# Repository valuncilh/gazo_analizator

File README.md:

<p align="center">
  <strong>Курсовой проект МАИ</strong><br>
  Учебный сигнализатор утечки метана (CH₄)
</p>

# Курсовой проект: сигнализатор утечки метана

**Рабочая ветка:** `analysis/vendor-behavioral-reconciliation`  
**Текущая конструктивная база:** локальная реализация E3, опубликованная в GitHub.  
**Статус:** проектная CAD-разработка и комплект РПЗ/КД в работе. ERC/DRC выполнены по подтверждению пользователя. Изделие не является сертифицированным средством защиты.

## Основные документы

- [Техническое задание (проект)](requirements/technical_assignment_draft.md)
- [Технические условия (проект)](requirements/technical_conditions_draft.md)
- [Матрица требований и проверок](requirements/verification_matrix.md)
- [Расчётно-пояснительная записка](docs/rpz/README.md)
- [Состав комплекта ЕСКД](docs/eskd_and_course_document_set.md)
- [Реестр документов и чертежей](docs/document_register.md)
- [Перечень элементов ПЭ3](docs/preliminary_element_list_PЭ3.md)
- [Правила заполнения основной надписи](docs/title_block_fill_guide.md)

## Текущий проект E3

Актуальные CAD-файлы:
- `cad/kicad/e3_project/gazo_e3_implementation.kicad_sch`
- `cad/kicad/e3_project/gazo_e3_implementation.kicad_pcb`
- `cad/kicad/e3_project/gazo_e3_implementation.kicad_pro`
- `cad/kicad/e3_project/fp-lib-table`
- библиотека применяемых footprints: `cad/kicad/footprints/GazoE3.pretty/`

Параметры PCB из файла: 59×45 мм, два медных слоя, FR-4 1,6 мм, 4 отверстия NPTH Ø2,2 мм с межосевыми расстояниями 52×37 мм, 19 функциональных компонентов, 206 сегментов трассировки, 21 via и 5 зон меди. Source-level сверка карты 47 pad-to-net с площадками PCB дала 47 совпадений. Пользователь подтвердил выполнение ERC/DRC и корректность ориентации A1/XS1 и полярности HA1/C1/C3. Повторные проверки не требуются в текущем цикле.

*Иллюстрация принципиальной схемы E3. Редактируемый источник схемы находится в `cad/kicad/e3_project/gazo_e3_implementation.kicad_sch`.*

## Формат чертежей

A3 используется как рабочий CAD-мастер, чтобы не ухудшать читаемость при разработке. Итоговый комплект графических документов планируется выдавать на A4 путём контролируемого уменьшения/переразмещения. После преобразования обязательно проверить текст, обозначения, линии, размеры, основную надпись и масштаб. Исходники A3 сохраняются.

## РПЗ и пример конструкторской документации

- Контрольная ODT-сборка РПЗ: [OneDrive](https://1drv.ms/w/c/24fda6920aa8c92a/IQBgvF5tTSGsRpjx8u47tfMPAWUgI9pUcU).
- Пример состава и оформления СБ/ВО, а также выбор ПО: [пример СБ и ВО](docs/examples/sb_vo_drawing_example.md).
- СБ/ВО рекомендуется выпускать в FreeCAD TechDraw по 3D-сборке. KiCad использовать для Э3 и ПП.

## Что уже сделано

- Создана и опубликована локальная реализация схемы и двухслойной PCB E3.
- В проект подключена собственная библиотека GazoE3 для SA1 и VT1.
- Подготовлена карта 47 назначений площадок к электрическим сетям.
- Подготовлены 11 глав рабочей РПЗ и расчётные материалы по питанию, теплу, надёжности и массогабаритам.
- Сформирован проектный перечень элементов ПЭ3 и перечень КД.
- Сформирована нормативная основа по ЕСКД, ТЗ и ТУ.

## Что осталось

- Разработать отдельную плату питания E4 с учётом расчётной нагрузки около 0,402 А и предварительного F1 T630 mA.
- Завершить почти готовую модель корпуса.
- Выпустить СБ и ВО в FreeCAD TechDraw на базе 3D-сборки по [примеру оформления](docs/examples/sb_vo_drawing_example.md). Для чертежа ПП использовать KiCad.
- Подготовить спецификацию по фактической PCB/BOM и составу сборки.
- Получить актуальную ODT-редакцию РПЗ из [OneDrive](https://1drv.ms/w/c/24fda6920aa8c92a/IQBgvF5tTSGsRpjx8u47tfMPAWUgI9pUcU) и синхронизировать с проектом.
- A4-выдачу отложить на следующий этап.

Физическое изготовление, лабораторная проверка, калибровка порога и сертификация не заявляются как выполненные.

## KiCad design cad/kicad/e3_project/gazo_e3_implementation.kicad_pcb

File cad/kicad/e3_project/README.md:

# E3 implementation project — isolated copy

**Status:** implementation scaffold / PRELIMINARY. This directory is separate from the immutable approved E3 source.

## Files

- `gazo_e3_implementation.kicad_sch` — copy of the approved E3 schematic with candidate physical footprints assigned in instance fields. Electrical topology, values, references, pins and nets are unchanged.
- `fp-lib-table` — project-local GazoE3 library path, resolved relative to this directory.
- `reports/e3_pad_net_map.csv` — 47 pin-to-net assignments derived from the approved XML-netlist.
- `reports/footprint_assignment_status.csv` — reference-level candidate status and restrictions.
- `reports/implementation_scaffold_validation.md` — source-content validation results and limitations.

## Footprint assignments

All 19 E3 references have a candidate footprint assignment. These are engineering candidates, not fabrication approval.

| Reference | Candidate footprint | Restriction |
|---|---|---|
| A1 | Molex PicoBlade 53261-0471 1x04 | Physical mapping of Molex pin 1 to sensor VCC/DOUT/AOUT/GND remains TBC. |
| C1, C3 | CP_Radial_D5.0mm_P2.00mm | Verify symbol polarity and mounting dimensions from the component drawing. |
| C2 | C_0805_2012Metric | Standard 0805 candidate. |
| DA1 | DIP-8_W7.62mm | TI NE555P PDIP-8 candidate. Approved symbol graphic remains NE555D. Verify pin-function parity in KiCad. |
| HA1 | GazoE3:HCM1206X_P7.6mm | Body dimensions documented. Positive physical lead remains TBC. |
| HL1, HL2 | LED_D5.0mm | Pad 1=cathode according to the symbol. Verify candidate MPN drawings. |
| R1–R7 | R_0805_2012Metric | 0805 candidates. Verify dissipation and current separately. |
| SA1 | GazoE3:NKK_AS11AP_SPST_P5.08mm | Pad 1/2 map to physical terminals 1/3. Actuator orientation remains a CAD enclosure constraint. |
| VD1 | D_DO-35_SOD27_P7.62mm_Horizontal | SELECTED candidate for KД-2 package. Pad 1=K, pad 2=A. KiCad 10 footprint validation remains pending. |
| VT1 | GazoE3:KT3102B_KT1-7_DWG_DRAFT | Drawing-derived draft. Pad 1=B, 2=C, 3=E. Upper-view coordinate interpretation remains TBC. |
| XS1 | Molex PicoBlade 53261-0271 1x02 | Pin 1=/VCC and pin 2=Earth per approved E3. Cable orientation remains TBC. |

## Immutable baseline

- Approved schematic Git blob SHA: `2e17299ba8a9aeeb0ce5e6c06562fe4e0fd84ba0`.
- Approved XML-netlist Git blob SHA: `b24384b2e1b39068b3a11c9e11554cd4dc406b57`.
- Expected topology: 19 components, 15 nets, 47 connected pins.

Do not edit the approved source schematic, XML-netlist or approved baseline to assign or refine implementation footprints. All further changes belong in this isolated implementation copy.

## Reproducible source-level check

From the repository root run:

```fish
python3 cad/scripts/verify_e3_implementation.py
```

The checker verifies the immutable source blob IDs, reversible-copy relationship, 19 footprint assignments, 47 pad-to-net rows and protected E3 nets. It does not run KiCad itself.

## Validation state

- Candidate footprint properties are present for all 19 references in this copy.
- Topology is inherited from the immutable approved schematic; native KiCad symbol-to-board netlist parity has not yet been run.
- KiCad 10 native validation, footprint checks and PCB DRC are pending. This remote editing session cannot execute the user's local KiCad 10.0.7 GUI/CLI.
- No PCB outline, placement, routing or manufacturing exports are created yet.
- No physical fit, assembly or laboratory validation is claimed.

## Local KiCad 10.0.7 acceptance gate

The next gate is deliberately local because the remote source-content checker cannot execute the user's KiCad installation.

1. Update the working branch locally. Do not create or restore `main`.
2. Open `gazo_e3_implementation.kicad_sch` in Eeschema. Confirm the schematic opens without missing symbols and inspect the project-local `GazoE3` footprint library path. The footprint table is `fp-lib-table` in this directory.
3. Run ERC and export a fresh XML-netlist using the KiCad 10 CLI.
4. Compare the fresh XML with the immutable approved netlist using the parity checker below.
5. Send the ERC report and parity output for review. Do not create or edit a PCB until topology parity is confirmed.

From the repository root, fish-compatible commands:

```fish
git fetch origin
git switch analysis/vendor-behavioral-reconciliation
git pull --ff-only origin analysis/vendor-behavioral-reconciliation

python3 cad/scripts/verify_e3_implementation.py

mkdir -p cad/kicad/e3_project/reports/local

kicad-cli version

kicad-cli sch erc --severity-all \
  --output cad/kicad/e3_project/reports/local/implementation_erc.rpt \
  cad/kicad/e3_project/gazo_e3_implementation.kicad_sch

kicad-cli sch export netlist --format kicadxml \
  --output cad/kicad/e3_project/reports/local/implementation_fresh.xml \
  cad/kicad/e3_project/gazo_e3_implementation.kicad_sch

python3 cad/scripts/compare_e3_netlists.py \
  --candidate cad/kicad/e3_project/reports/local/implementation_fresh.xml

python3 cad/scripts/compare_e3_netlists.py \
  --candidate cad/kicad/e3_project/reports/local/implementation_fresh.xml \
  --require-footprints
```

The first comparison checks the 19 component references/values, all 15 nets and 47 connected pins, plus the protected `/AOUT` and `Net-(SA1-B)` connections. The second also requires a non-empty Footprint field for all 19 components. If the second check reports missing footprint fields, keep the topology result separate and send the XML for investigation.

**ERC is a report, not an automatic pass/fail command here.** The command intentionally omits `--exit-code-violations`, so warnings can be reviewed without treating every warning as a shell failure. Do not suppress warnings or alter the approved schematic to make the report clean.

KiCad 10 CLI syntax is documented in the [official KiCad 10 reference](https://docs.kicad.org/10.0/en/cli/cli.html). ERC usage is `kicad-cli sch erc`; XML export uses `kicad-cli sch export netlist --format kicadxml`.

Do not create `.kicad_pro` or `.kicad_pcb` files yet. They are the next remote CAD step only after the local gate confirms schematic loading, library resolution, ERC review and XML parity.

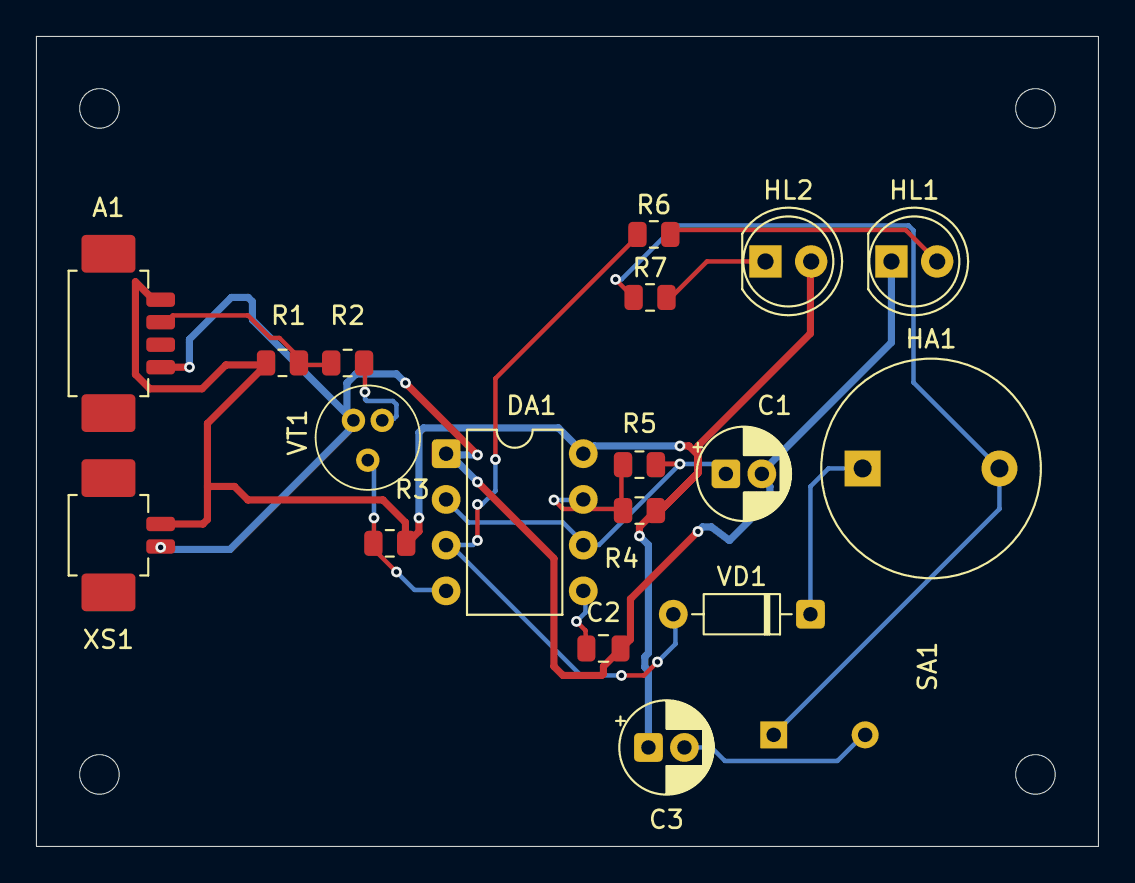
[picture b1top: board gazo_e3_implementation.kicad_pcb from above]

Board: 2 copper layers, 59.0 x 45.0 mm, 23 parts (0 on the bottom side), 14 nets.

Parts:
A1: Датчик метана Joy-IT SEN-MQ4-V2; Molex_PicoBlade_53261-0471_1x04-1MP_P1.25mm_Horizontal
C1, C3: 47 000 000 пФ, 16 В; CP_Radial_D5.0mm_P2.00mm
C2: 100 000 пФ; C_0805_2012Metric
DA1: NE555P; DIP-8_W7.62mm
HA1: HCM1206X; Buzzer_12x9.5RM7.6
HL1: Красный светодиод; LED_D5.0mm
HL2: Зелёный светодиод; LED_D5.0mm
MH1, MH2, MH3, MH4: Ø2,2 NPTH; MountingHole_2.2mm_M2
R1: 160 кОм; R_0805_2012Metric
R2: 13 кОм; R_0805_2012Metric
R3: 2 кОм; R_0805_2012Metric
R4, R5: 8,2 кОм; R_0805_2012Metric
R6, R7: 0,22 кОм; R_0805_2012Metric
SA1: Включение звукового сигнала; NKK_AS11AP_SPST_P5.08mm
VD1: КД510А; D_DO-35_SOD27_P7.62mm_Horizontal
VT1: КТ3102Б; KT3102B_KT1-7_DWG_DRAFT
XS1: Molex_PicoBlade_53261-0271_1x02-1MP_P1.25mm_Horizontal

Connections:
/VCC: A1.1, C3.1, DA1.8 (VCC), HL2.2 (A), R1.1, R3.2, R4.2, XS1.1
Earth: A1.4, C1.2, C2.2, DA1.1 (GND), HL1.1 (K), VT1.3 (E), XS1.2
unnamed: A1.2, R1.2, R2.1
unnamed: C2.1, DA1.5 (CONT)
unnamed: DA1.7 (DISCH), R4.1, R5.1
unnamed: DA1.3 (OUT), R6.1, VD1.2 (A)
unnamed: C1.1, DA1.2 (TRIG), DA1.6 (THRES), R5.2
unnamed: DA1.4 (~RST), R3.1, VT1.2 (C)
unnamed: HA1.1 (+), VD1.1 (K)
unnamed: HA1.2 (-), R7.1, SA1.1 (A)
unnamed: HL1.2 (A), R6.2
unnamed: HL2.1 (K), R7.2
unnamed: C3.2, SA1.2 (B)
unnamed: R2.2, VT1.1 (B)

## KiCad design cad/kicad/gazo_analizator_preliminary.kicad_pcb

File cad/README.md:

# CAD: historical preliminary placement and current E3/E4 design

The original iteration below is **HISTORICAL / SUPERSEDED**. Current design requirements are in [pcb_design_basis_2026-11-01.md](pcb_design_basis_2026-11-01.md). No manufacturing release is implied.

## Iteration 0.1

- Native KiCad PCB placement draft: 72 x 50 x 1.6 mm, net assignments and custom in-file footprints.
- No copper routing is present. DRC unconnected-net warnings are expected and are not a pass for manufacturing.
- This historical placement used a separate 25.4 x 25.4 mm Amperka AMP-B052 module. The current design uses Joy-IT SEN-MQ4-V2 and does not reuse this mechanical placement.
- A parametric FreeCAD case concept is provided at 120 x 78 x 42 mm. It includes a removable lid, standoffs, module rails, MQ-4 vent grid, HCM1205X aperture, LED holes and a provisional power connector cutout.
- The selected JL World HCM1205X dimensions come from passport 0105-86 Rev. A2: body OD 12 mm, height about 9.5 mm, lead pitch 7.6 mm. The MQ-4 sensor can profile is still a TBC envelope.

## Critical TBC items

1. KT3102GM manufacturer-specific pinout, package drawing and saturation at the required collector current.
2. The physical P1 trim potentiometer, SA1 DPDT switch and XS1 power connector.
3. Exact resistor, capacitor, LED and diode footprints.
4. KiCad schematic, ERC, netlist parity, PCB routing and DRC closure.
5. Actual A1 mounting method, MQ-4 sensor height, ventilation and heat clearances.
6. Acoustic clearance and lid light-pipe fit.
7. Formal mechanical test levels and any required ingress-protection criteria.

## Sources

- Amperka AMP-B052: https://amperka.ru/product/troyka-mq4-gas-sensor and https://wiki.amperka.ru/продукты:mq4.
- JL World HCM1205X, Specification 0105-86 Rev. A2: https://satec.ru/_img/goods_attach/474/00-00135474/134038_0.pdf.
- KR1006VI1, package 2101.8-1: https://radiolub.ru/uploads/2012pic/kr1006vi1.pdf.
- KiCad PCB file format: https://dev-docs.kicad.org/en/file-formats/sexpr-pcb/.
- KiCad CLI: https://docs.kicad.org/9.0/en/cli/cli.html.
- FreeCAD headless usage: https://github.com/FreeCAD/FreeCAD-documentation/blob/main/wiki/Headless_FreeCAD.md.

## Next gate

Create a native KiCad schematic and validate its pin mapping before routing. Replace all TBC footprints with exact selected manufacturer footprints, run ERC/DRC, then issue production files only after the thermal/current/case mechanical blockers have been reviewed.

## Electrical trace audit

The [historical electrical trace audit](electrical_trace_audit_2026-10-25.md) describes the Amperka A1.S path and an alternative comparator design. It is not the current Joy-IT E3 signal path and must not be used to populate the current PCB.

Run `python3 cad/scripts/test_electrical_trace.py` locally to compare declared SPICE nodes against the provisional PCB pad-net map. This is a topology consistency check, not a measurement of copper continuity.

Latest completed physical-layout checks before the trace regression was added:

- KiCad pad-net map: 27 expected footprints and 72 pad assignments matched.
- KiCad DRC: 0 geometry violations, but 53 unconnected items.
- Copper tracks: 0. The PCB is still **UNROUTED**.
- Preliminary FreeCAD FCStd, STEP and STL exports were generated in an earlier model build. Their geometry and fit still require manual review against the selected components.

Do not generate manufacturing files from this draft. The native schematic/ERC/netlist parity, exact component pinouts and footprints, copper routing and physical fit checks remain open.

## Проектная схема Э3 по ЕСКД

Проектная электрическая принципиальная схема CH₄ оформляется отдельным комплектом и не смешивается с транскрипцией Original 2022. Проверяемые критерии оформления, электрической топологии, ERC и выдаваемых артефактов находятся в [критериях приёмки Э3](project_modification_eskd/acceptance_criteria.md).

Перед переносом экспериментальной компоновки в репозиторий необходимо перенести её исходный генератор, эталонную таблицу и локальные результаты KiCad. До этого локальный PASS не является воспроизводимой проверкой из текущего Git-состояния. Все результаты остаются **PRELIMINARY / NOT FOR FABRICATION**.

Первичная таблица соответствия символов и координат выводов: [аудит GOST-символов](project_modification_eskd/symbol_mapping.md). Это карта кандидатов, не финальная приёмка УГО.

Методическая основа формата: [анализ материалов МАИ](project_modification_eskd/mai_methodical_basis.md). Для текущего курсового проекта выбран A4 по пособию МАИ 2007, раздел 1.3, печатная с. 5. A1 в этом пособии относится к графической части дипломного проекта и не применяется к нашей курсовой.

Для листа A4 установлена книжная ориентация и размещение основной надписи вдоль короткой стороны по ГОСТ Р 2.104-2023, приложение Б, Б.5. Альбомное A4 не использовать.

## Current design selection — 01.11.2026

The selected sensor is Joy-IT SEN-MQ4-V2. The approved E3 schematic remains unchanged. A1 uses the Molex PicoBlade 53261-0471 candidate and XS1 uses 53261-0271. The physical A1 Molex pin-1 mapping to VCC/DOUT/AOUT/GND is not explicit in the available module documentation and remains TBC; no physical continuity test is part of this CAD-only project. USB-C is on a separate two-layer E4 power-entry PCB. Current MPN and package restrictions are documented in [footprint_selection_2026-11-01.md](footprint_selection_2026-11-01.md), [the 02.11.2026 footprint audit](footprint_audit_2026-11-02.md), and [power_input_usb/README.md](power_input_usb/README.md).

A preliminary FreeCAD sensor envelope macro is provided at `freecad/build_joyit_sen_mq4_v2_envelope.FCMacro`. It has not yet been executed or checked in FreeCAD. The main enclosure must be designed after the actual E3 and E4 PCB layouts and the sensor module envelope have been verified.

## Frozen E3 PCB routing basis — 01.11.2026

- Exact net-to-pin map: [`e3_netlist_map_2026-11-01.md`](e3_netlist_map_2026-11-01.md)
- Placement and routing priority: [`placement_plan_joyit_e3_2026-11-01.md`](placement_plan_joyit_e3_2026-11-01.md)
- Netlist regression: `python3 cad/scripts/verify_e3_netlist.py`

These files describe the approved E3 logical topology only. They do not claim that the board has been placed, routed, or DRC-checked.

## E3 implementation project scaffold

An isolated implementation copy is prepared in [`kicad/e3_project/`](kicad/e3_project/). It contains:
- `gazo_e3_implementation.kicad_sch` — implementation copy of the approved E3 schematic, with candidate footprint fields assigned to all 19 physical references. The source schematic remains immutable.
- `fp-lib-table` — local GazoE3 footprint library registration.
- `reports/e3_pad_net_map.csv` — 47 pin-to-net assignments.
- `reports/footprint_assignment_status.csv` — 19-reference candidate/restriction register.
- `reports/implementation_scaffold_validation.md` — source-level baseline and copy-integrity report.

Run `python3 cad/scripts/verify_e3_implementation.py` from the repository root for source-level checks of the implementation copy and immutable schematic/netlist blob IDs. The [source validation report](kicad/e3_project/reports/implementation_scaffold_validation.md) records the current remote content check. This script does not replace KiCad 10 validation.

No `.kicad_pro` or `.kicad_pcb` has been created in this scaffold yet. The next gate is to open the implementation schematic in KiCad 10.0.7, confirm the project-local GazoE3 library resolves, run ERC and export a fresh XML-netlist. Only after topology parity is confirmed should the board file be created.

## Approved E3 placement and routing plan

The current placement zones and routing priorities derived from the immutable approved XML-netlist are documented in [`placement/e3_placement_plan.md`](placement/e3_placement_plan.md). Conceptual zone diagram: [`placement/e3_placement_zones.svg`](placement/e3_placement_zones.svg).

The netlist audit script is [`scripts/verify_e3_netlist.py`](scripts/verify_e3_netlist.py). The 47-row exported [pad-to-net map](project_modification/gost_e3_final/reports/kicad10/e3_pad_net_map.csv) is committed next to the approved KiCad reports. Run the audit locally from the repository root with:

```fish
python3 cad/scripts/verify_e3_netlist.py --write-csv
```

The script checks the approved XML blob, all 19 component values, 15 exact nets and 47 connected pins, and exports a pad-to-net CSV. It is a topology check only, not KiCad DRC.

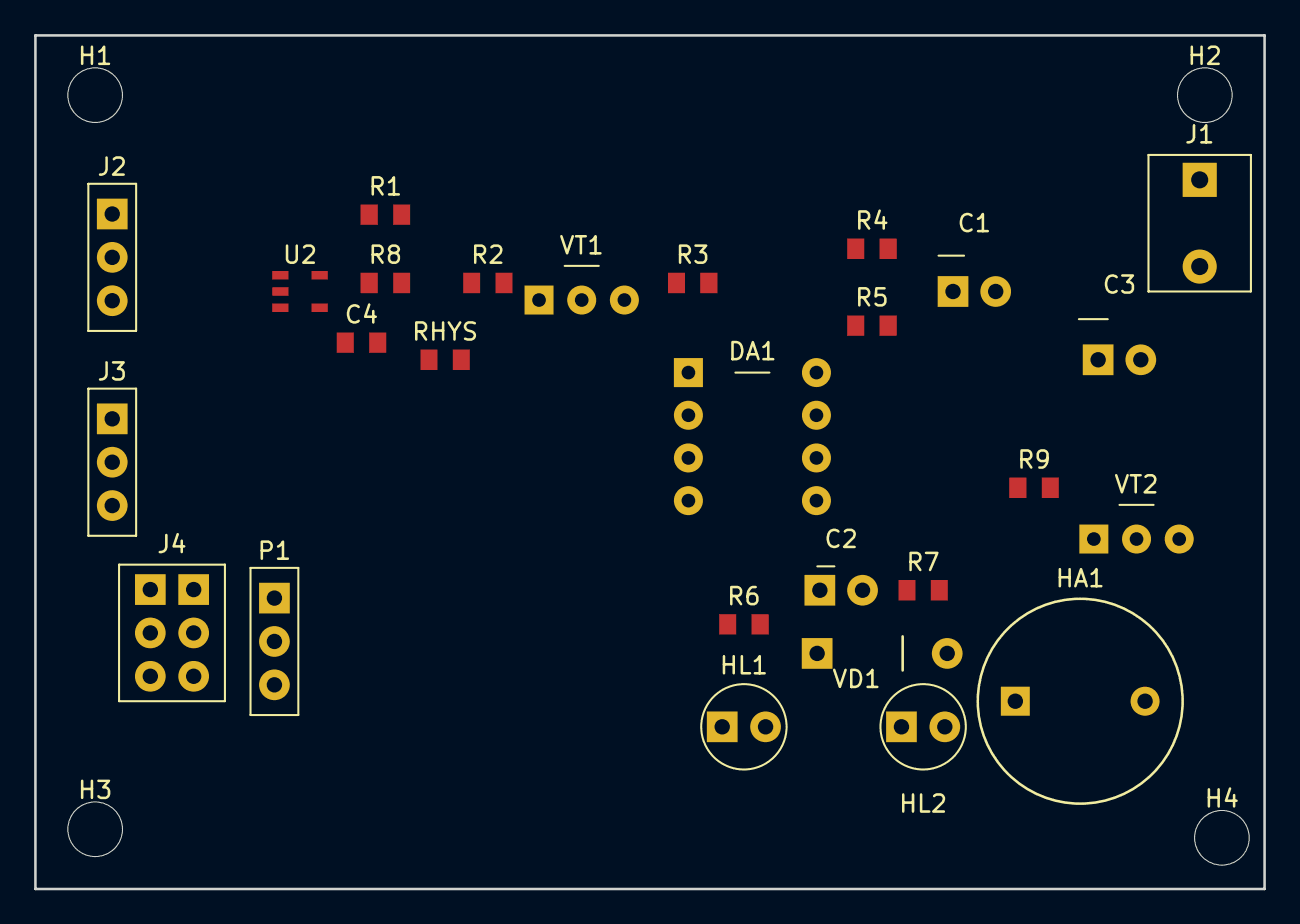
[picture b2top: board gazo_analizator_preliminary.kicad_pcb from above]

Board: 2 copper layers, 72.0 x 50.0 mm, 31 parts (0 on the bottom side), 17 nets, no tracks yet.

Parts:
C1: 4.7uF TBC; Capacitor_THT_2.50mm_TBC_R3
C2: 100nF TBC; Capacitor_THT_2.50mm_TBC_R2
C3: 47uF TBC; Capacitor_THT_2.50mm_TBC_R3p4
C4: 100nF U2 bypass; C_0805_TBC
DA1: KR1006VI1; KR1006VI1_2101.8-1_P2.50x7.50_TBC
H1, H2, H3, H4: M3_CLR; MountingHole_M3_TBC
HA1: JL WORLD HCM1205X; Buzzer_HCM1205X_P7.6_TBC
HL1: RED 5mm TBC; LED_D5.0mm_P2.54_TBC
HL2: GREEN 5mm TBC; LED_D5.0mm_P2.54_TBC
J1: XS1 5V INPUT; PowerIn_1x2_P5.08_TBC
J2: A1 SIGNAL S/V/G; PinHeader_1x3_P2.54_TBC
J3: A1 HEATER E/H/G; PinHeader_1x3_P2.54_TBC
J4: SA1 DPDT SWITCH; SA1_DPDT_2Pole_2.54_TBC
P1: 10k POT TBC; PinHeader_1x3_P2.54_TBC
R1: 160k; R_0805_TBC
R2: 10k; R_0805_TBC
R3: 2k; R_0805_TBC
R4, R5: 8.2k; R_0805_TBC
R6, R7: 220R; R_0805_TBC
R8: 2.2k; R_0805_TBC
R9: 560R; R_0805_TBC
RHYS: 100k; R_0805_TBC
U2: TLV7041-Q1; TLV7041Q_SOT23-5_TBC
VD1: KD510A TBC; Diode_Axial_P7.62_TBC
VT1: KT3102GM / VT1; KT26_KT3102GM_PINOUT_TBC
VT2: KT3102GM / VT2; KT26_KT3102GM_PINOUT_TBC

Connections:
+5V: C3.1, C4.1, DA1.8, HA1.1, J1.1, J2.2, J3.1, J3.2, P1.1, R1.1, R3.1, R4.1, R7.1, R8.1, U2.5, VD1.2
BUZZ_COL: HA1.2, VD1.1, VT2.1
DOUT: R1.2, R2.1, R8.2, RHYS.1, U2.1
GND: C1.2, C2.2, C3.2, C4.2, DA1.1, HL1.2, J1.2, J2.3, J3.3, J4.4, P1.3, U2.2, VT1.3, VT2.3
HL1_A: HL1.1, R6.2
HL2_A: HL2.1, R7.2
OUT: DA1.3, J4.2, R6.1
RESET: DA1.4, R3.2, VT1.1
SA1_LED_RETURN: HL2.2, J4.5
SENSE: J2.1, U2.4
SOUND_CTL: J4.1, R9.1
TIMER_CT: C1.1, DA1.2, DA1.6, R5.2
TIMER_CTRL: C2.1, DA1.5
TIMER_DISCH: DA1.7, R4.2, R5.1
UREF: P1.2, RHYS.2, U2.3
VT1_BASE: R2.2, VT1.2
VT2_BASE: R9.2, VT2.2

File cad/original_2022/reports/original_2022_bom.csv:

"Refs","Value","Footprint","Qty","DNP"
"A1","MQ-4 module (model unknown)","","1",""
"C1","4.7 µF 16 V","","1",""
"C2","100 n (as printed)","","1",""
"C3","47 µF 16 V","","1",""
"DA1","NE555N","","1",""
"HA1","HCM1206X or equivalent","","1",""
"HL1","Red LED","","1",""
"HL2","Green LED","","1",""
"R1","160 kΩ","","1",""
"R2","13 kΩ","","1",""
"R3","2 kΩ","","1",""
"R4","8.2 kΩ","","1",""
"R5","8.2 kΩ","","1",""
"R6","220 Ω","","1",""
"R7","220 Ω","","1",""
"SA1","Sound enable","","1",""
"VD1","КД510А","","1",""
"VT1","КТ3102Б","","1",""
"XS1","5 V input","","1",""
